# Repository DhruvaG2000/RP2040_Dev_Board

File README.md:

# RP2040_Dev_Board
Kicad PCB design for a RP2040 Development Board Designed to make the RP2040 more beginner friendly
## Features to Implement
- [X] Add Female headers to the PCB to directly connect with pico
- [X] Add 12V/5V and 3.3V Power with reverse polarity protection
- [ ] Add LEDs
  - [X] Power LED
  - [ ] Blink LED
- [ ] Add Battery power circuit    
- [ ] Add slots for Basic sensors like DHT11, 22, LDR, etc.
- [ ] Add motor driver for stepper, DC, BLDC etc.
- [ ] Add protection circuit
- [ ] Add I2C, SPI, UART interfaces in the form of connectors to communicate with external MCUs
## Pico Pin Diagram

## Preview
### 3D render of current status of the project:

### Schematic layout:

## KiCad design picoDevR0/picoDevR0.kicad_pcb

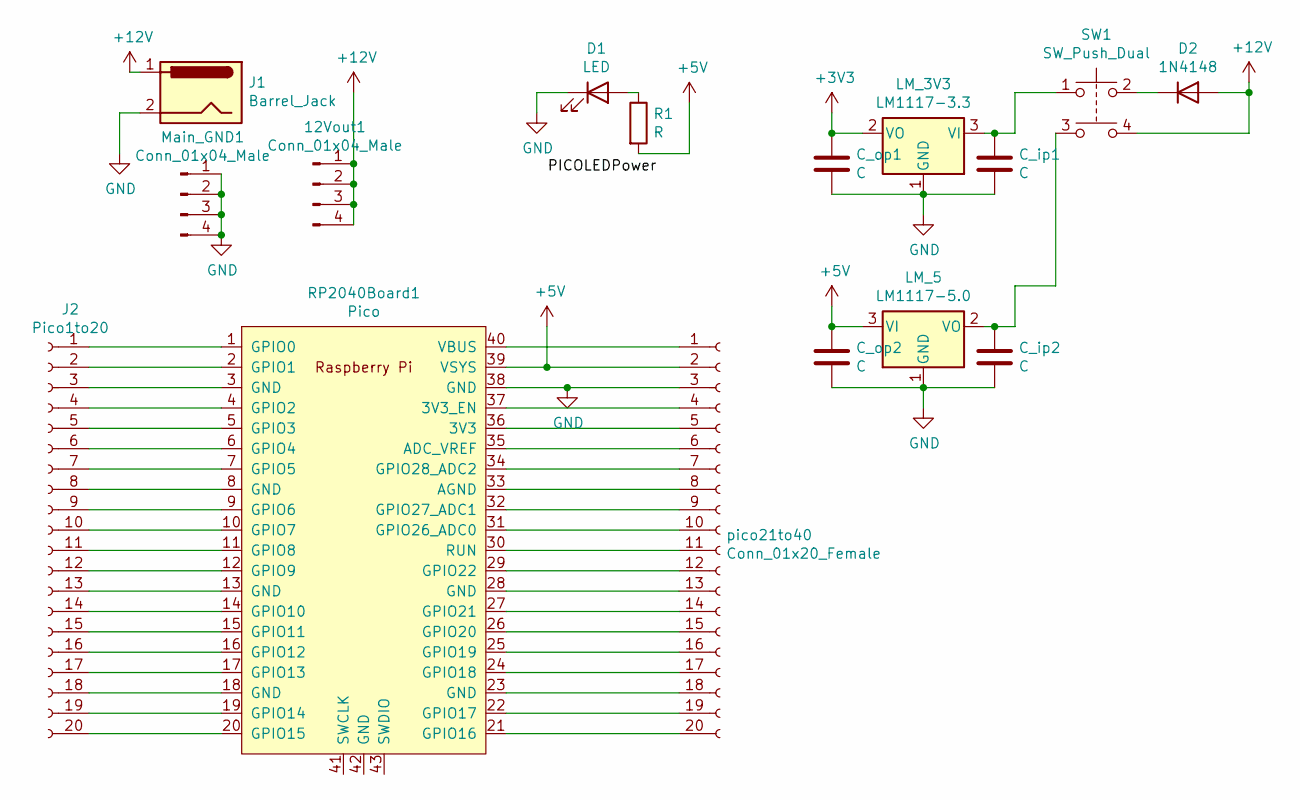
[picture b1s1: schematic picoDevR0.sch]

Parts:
12Vout1: Conn_01x04_Male; PinHeader_1x04_P1.00mm_Vertical
C_ip1, C_ip2: C; CP_Radial_D10.0mm_P2.50mm
C_op1, C_op2: C; CP_Radial_D10.0mm_P2.50mm
D1: LED; LED_D4.0mm
D2: 1N4148; D_DO-35_SOD27_P7.62mm_Horizontal
J1: Barrel_Jack; BarrelJack_CUI_PJ-063AH_Horizontal
J2: Pico1to20; PinSocket_1x20_P2.54mm_Vertical
LM_3V3: LM1117-3.3; PinSocket_1x03_P1.00mm_Vertical
LM_5: LM1117-5.0; PinSocket_1x03_P1.00mm_Vertical
Main_GND1: Conn_01x04_Male; PinHeader_1x04_P1.00mm_Vertical
R1: R; R_Axial_DIN0411_L9.9mm_D3.6mm_P25.40mm_Horizontal
RP2040Board1: Pico; RPi_Pico_SMD_TH
SW1: SW_Push_Dual; Push_E-Switch_KS01Q01
pico21to40: Conn_01x20_Female; PinSocket_1x20_P2.54mm_Vertical

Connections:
+3V3: C_op1.1, LM_3V3.2 (VO)
+5V: C_op2.1, LM_5.3 (VI), R1.2, RP2040Board1.39 (VSYS), pico21to40.2
+12V: 12Vout1.1, 12Vout1.2, 12Vout1.3, 12Vout1.4, D2.2 (A), J1.1, SW1.4
GND: C_ip1.2, C_ip2.2, C_op1.2, C_op2.2, D1.1 (K), J1.2, LM_3V3.1 (GND), LM_5.1 (GND), Main_GND1.1, Main_GND1.2, Main_GND1.3, Main_GND1.4, RP2040Board1.38 (GND), pico21to40.3
unnamed: C_ip1.1, LM_3V3.3 (VI), SW1.1
unnamed: C_ip2.1, LM_5.2 (VO), SW1.3
unnamed: D1.2 (A), R1.1
unnamed: D2.1 (K), SW1.2
unnamed: J2.1, RP2040Board1.1 (GPIO0)
unnamed: J2.2, RP2040Board1.2 (GPIO1)
unnamed: J2.3, RP2040Board1.3 (GND)
unnamed: J2.4, RP2040Board1.4 (GPIO2)
unnamed: J2.5, RP2040Board1.5 (GPIO3)
unnamed: J2.6, RP2040Board1.6 (GPIO4)
unnamed: J2.7, RP2040Board1.7 (GPIO5)
unnamed: J2.8, RP2040Board1.8 (GND)
unnamed: J2.9, RP2040Board1.9 (GPIO6)
unnamed: J2.10, RP2040Board1.10 (GPIO7)
unnamed: J2.11, RP2040Board1.11 (GPIO8)
unnamed: J2.12, RP2040Board1.12 (GPIO9)
unnamed: J2.13, RP2040Board1.13 (GND)
unnamed: J2.14, RP2040Board1.14 (GPIO10)
unnamed: J2.15, RP2040Board1.15 (GPIO11)
unnamed: J2.16, RP2040Board1.16 (GPIO12)
unnamed: J2.17, RP2040Board1.17 (GPIO13)
unnamed: J2.18, RP2040Board1.18 (GND)
unnamed: J2.19, RP2040Board1.19 (GPIO14)
unnamed: J2.20, RP2040Board1.20 (GPIO15)
unnamed: RP2040Board1.21 (GPIO16), pico21to40.20
unnamed: RP2040Board1.22 (GPIO17), pico21to40.19
unnamed: RP2040Board1.23 (GND), pico21to40.18
unnamed: RP2040Board1.24 (GPIO18), pico21to40.17
unnamed: RP2040Board1.25 (GPIO19), pico21to40.16
unnamed: RP2040Board1.26 (GPIO20), pico21to40.15
unnamed: RP2040Board1.27 (GPIO21), pico21to40.14
unnamed: RP2040Board1.28 (GND), pico21to40.13
unnamed: RP2040Board1.29 (GPIO22), pico21to40.12
unnamed: RP2040Board1.30 (RUN), pico21to40.11
unnamed: RP2040Board1.31 (GPIO26_ADC0), pico21to40.10
unnamed: RP2040Board1.32 (GPIO27_ADC1), pico21to40.9
unnamed: RP2040Board1.33 (AGND), pico21to40.8
unnamed: RP2040Board1.34 (GPIO28_ADC2), pico21to40.7
unnamed: RP2040Board1.35 (ADC_VREF), pico21to40.6
unnamed: RP2040Board1.36 (3V3), pico21to40.5
unnamed: RP2040Board1.37 (3V3_EN), pico21to40.4
unnamed: RP2040Board1.40 (VBUS), pico21to40.1

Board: 4 copper layers, 16 parts (0 on the bottom side), 46 nets, no tracks yet.

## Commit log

2021-04-07 First photo
2021-04-07 removed false br
2021-04-07 added library
2021-04-07 remove .gitignore
2021-04-07 added pinout
2021-04-07 added photo
2021-04-07 to do
2021-05-14 added barrel, have to fix switch and add connections
2021-05-14 added one-one pin connections in sch
2021-05-14 added pin 1:1, barrel power, LED|switch needs fix
2021-05-14 updated photos
2021-05-15 replaced switch and LED
    replaced earlier component with 2 seperate one's for ease of footprint assigning
2021-05-15 LM footprint changed to female
    also there seems to be an issue with the button footprint, need one proper 2-hole button
2021-05-15 fix switch and barrel jack
    fixed only in sch, need changes in the PCBNew
2021-05-15 Increased GND path width
    Increased the 12V to switch and GND path widths to allow higher current. This can be particularly useful if we are going to add motor drivers and attach motors directly to the board.
    opinion: shud I add external 3V3 or not needed? (I think not)
    future work: Add slots for DHT11/ 22
2021-05-15 daily updates
2021-05-15 checked and added some more TODOs
2021-05-16 changed LED and resistor footprint
    earlier one's were too big
2021-05-16 added gnd layer
    and removed all the gnd paths that were in place earlier
2021-05-16 added capacitors to LDO
    and also made the sch more neat by adding 5V, 12V and GND labels.
2021-05-16 added 3v3 and 5V seperate LMs
2021-05-16 added 5V layer
    added everything to the PCB.
    issues: 5V layer is not getting connected with the pico Vcc and the LED resistor for some reason, needs debugging.
2021-05-16 updated README
    Updated photos
2021-05-16 minor fix in path
2021-05-16 addded reverse polarity in checklist
2021-05-17 reset everything in the PCB
    There were many issues with the earlier approach of constantly making changes in the PCB layer after sch like the 5V layer wasn't being accessed by some pins, and so on. Hence it is decided that henc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
